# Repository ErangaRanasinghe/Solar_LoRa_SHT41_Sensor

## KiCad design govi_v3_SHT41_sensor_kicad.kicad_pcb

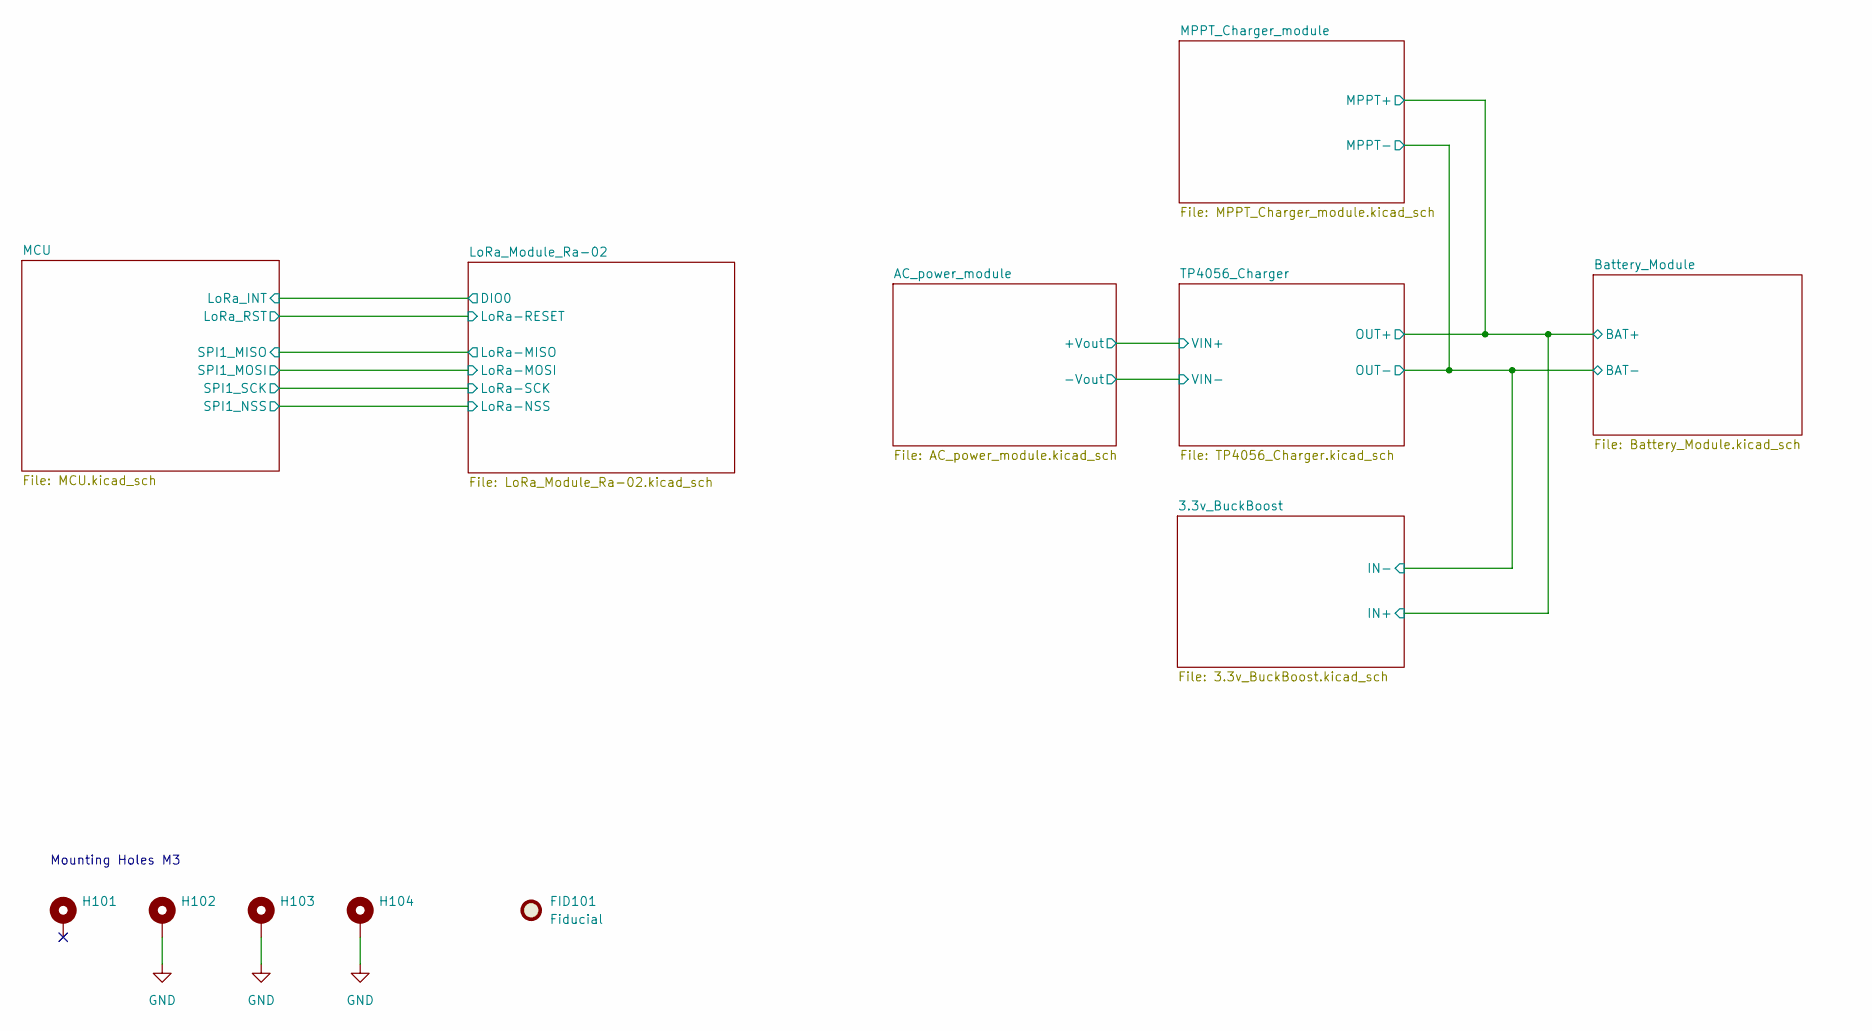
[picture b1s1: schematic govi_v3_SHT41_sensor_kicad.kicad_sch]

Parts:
FID101: Fiducial; Fiducial_1mm_Mask3mm
H101, H102, H103, H104: MountingHole_Pad; MountingHole_3.2mm_M3_Pad_TopBottom

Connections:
GND: H102.1, H103.1, H104.1; also elsewhere on the board

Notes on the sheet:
Mounting Holes M3

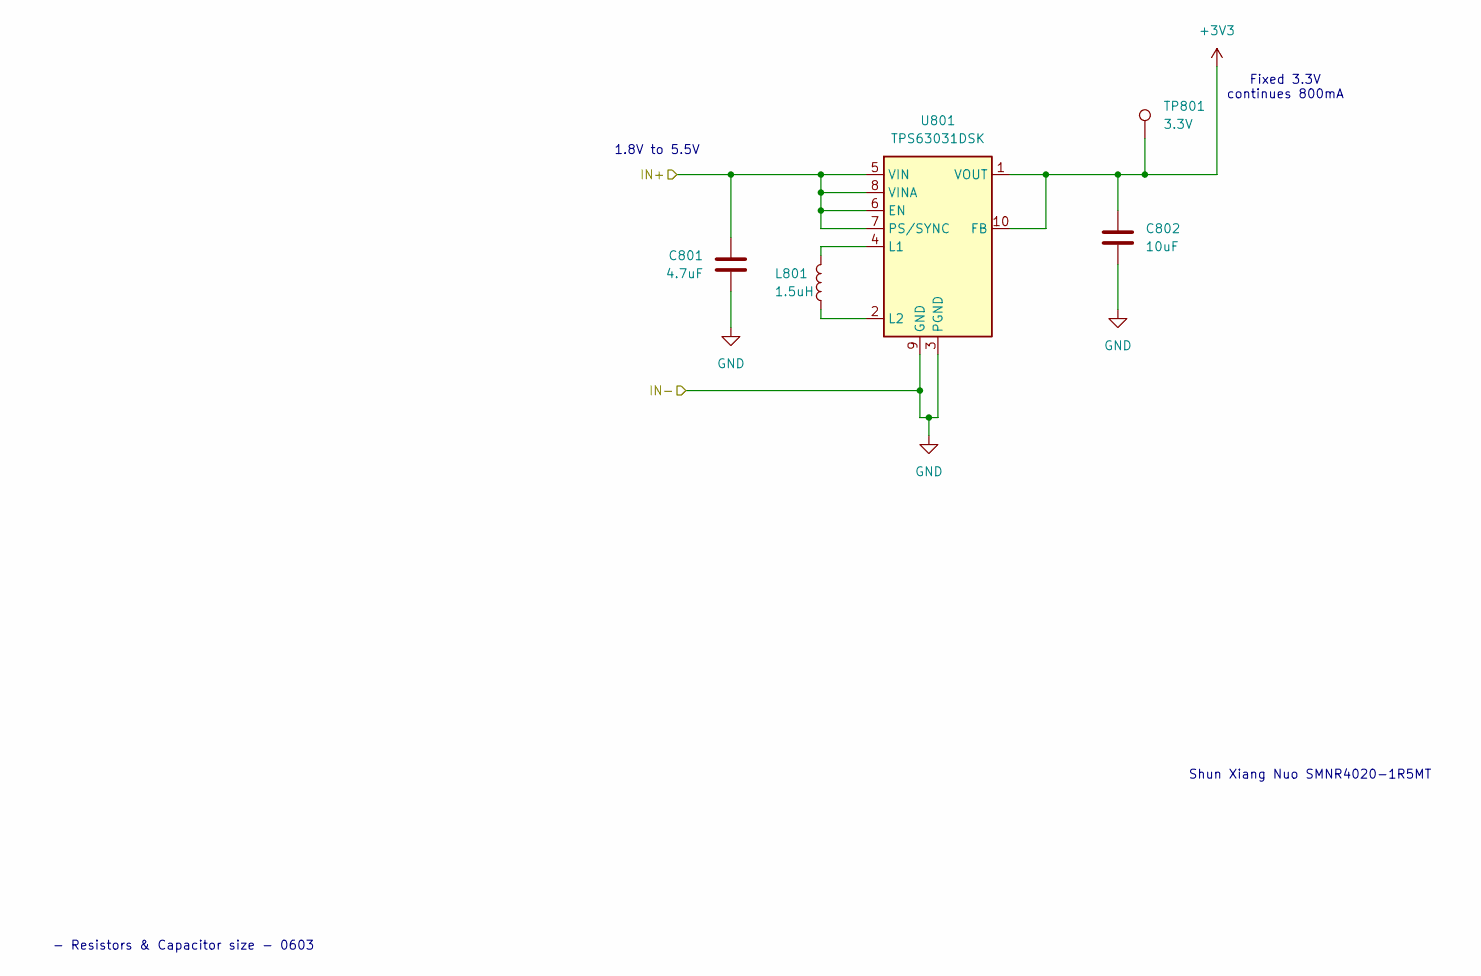
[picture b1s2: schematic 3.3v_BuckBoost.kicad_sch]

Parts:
C801: 4.7uF; C_0603_1608Metric_Pad1.08x0.95mm_HandSolder
C802: 10uF; C_0603_1608Metric_Pad1.08x0.95mm_HandSolder
L801: 1.5uH; L_Wurth_WE-LQSH-4020
TP801: 3.3V; TestPoint_Pad_D1.0mm
U801: TPS63031DSK; WSON-10-1EP_2.5x2.5mm_P0.5mm_EP1.2x2mm

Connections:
+3V3: C802.1, TP801.1, U801.1 (VOUT), U801.10 (FB); also elsewhere on the board
/3.3v_BuckBoost/IN+: C801.1, U801.5 (VIN), U801.6 (EN), U801.7 (PS/SYNC), U801.8 (VINA); also elsewhere on the board
GND: C801.2, C802.2, U801.3 (PGND), U801.9 (GND), U801.11 (PGND); also elsewhere on the board
unnamed: L801.1, U801.4 (L1)
unnamed: L801.2, U801.2 (L2)

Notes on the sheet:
Shun Xiang Nuo SMNR4020-1R5MT
- Resistors & Capacitor size - 0603
1.8V to 5.5V
Fixed 3.3V continues 800mA

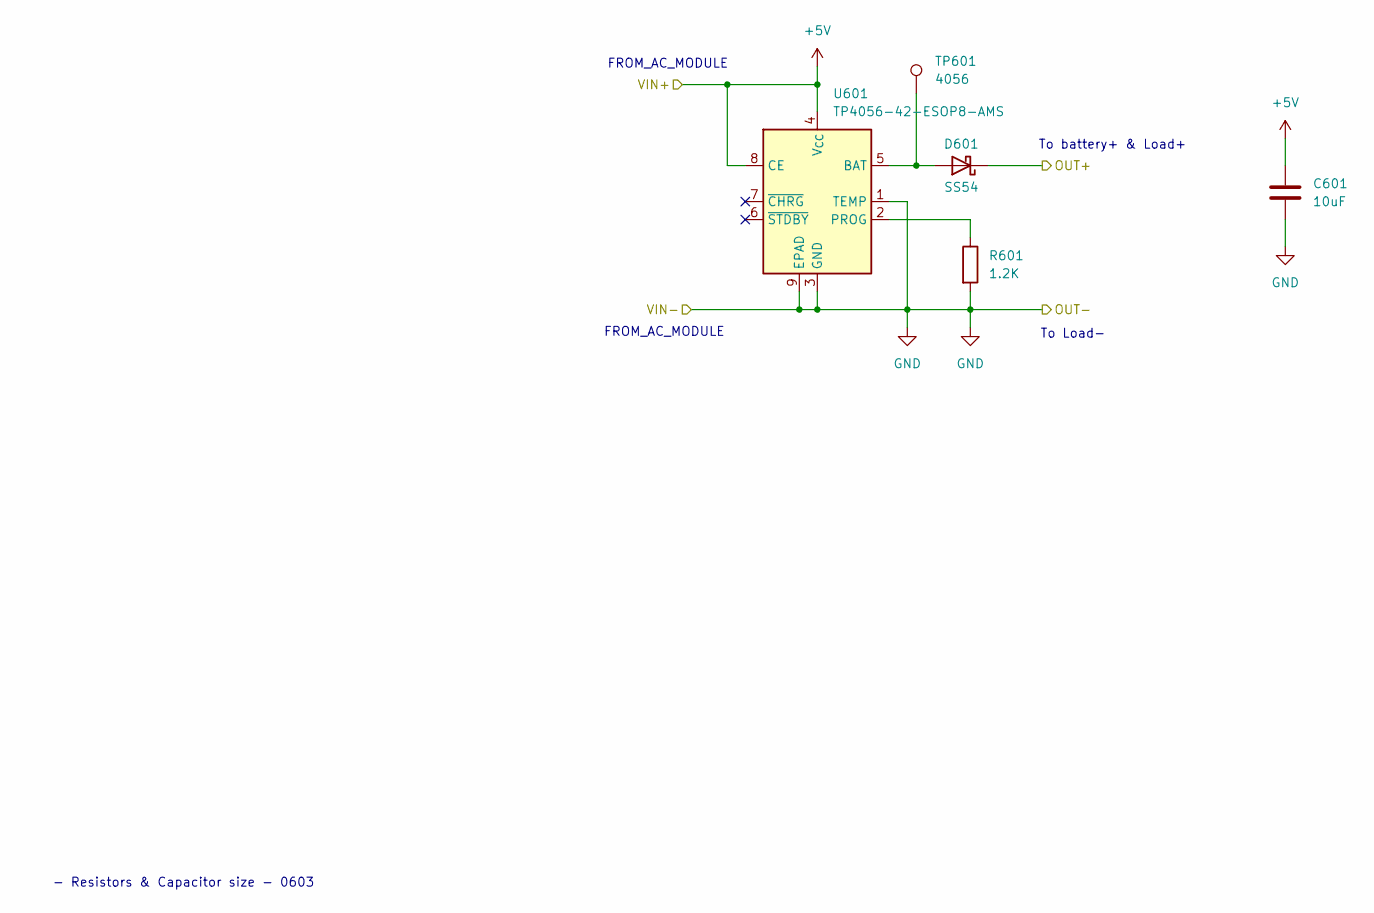
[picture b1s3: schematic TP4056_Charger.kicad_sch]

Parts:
C601: 10uF; C_0603_1608Metric_Pad1.08x0.95mm_HandSolder
D601: SS54; D_SMA
R601: 1.2K; R_0603_1608Metric_Pad0.98x0.95mm_HandSolder
TP601: 4056; TestPoint_Pad_D1.0mm
U601: TP4056-42-ESOP8-AMS; SOIC-8-1EP_3.9x4.9mm_P1.27mm_EP2.41x3.3mm_ThermalVias

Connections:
+5V: C601.1, U601.4 (V_{CC}), U601.8 (CE); also elsewhere on the board
/3.3v_BuckBoost/IN+: D601.1 (K); also elsewhere on the board
GND: C601.2, R601.2, U601.1 (TEMP), U601.3 (GND), U601.9 (EPAD); also elsewhere on the board
unnamed: D601.2 (A), TP601.1, U601.5 (BAT)
unnamed: R601.1, U601.2 (PROG)

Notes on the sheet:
- Resistors & Capacitor size - 0603
To battery+ & Load+
To Load-
FROM_AC_MODULE

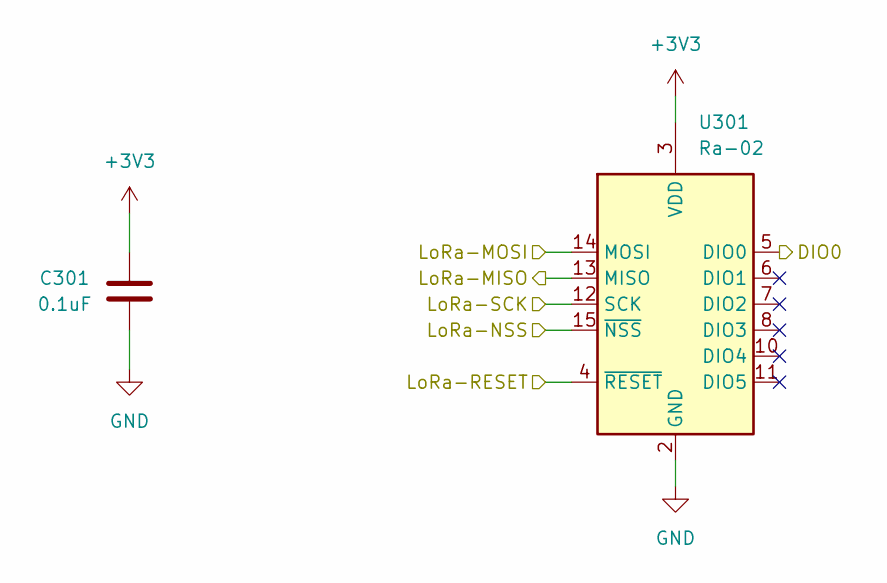
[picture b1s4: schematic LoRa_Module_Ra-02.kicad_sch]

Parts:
C301: 0.1uF; C_0402_1005Metric_Pad0.74x0.62mm_HandSolder
U301: Ra-02; Ai-Thinker-Ra-01-LoRa

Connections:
+3V3: C301.1, U301.3 (VDD); also elsewhere on the board
/LoRa_Module_Ra-02/LoRa-MISO: U301.13 (MISO); also elsewhere on the board
/LoRa_Module_Ra-02/LoRa-MOSI: U301.14 (MOSI); also elsewhere on the board
/LoRa_Module_Ra-02/LoRa-NSS: U301.15 (~NSS); also elsewhere on the board
/LoRa_Module_Ra-02/LoRa-RESET: U301.4 (~RESET); also elsewhere on the board
/LoRa_Module_Ra-02/LoRa-SCK: U301.12 (SCK); also elsewhere on the board
/MCU/LoRa_INT: U301.5 (DIO0); also elsewhere on the board
GND: C301.2, U301.1 (GND), U301.2 (GND), U301.9 (GND), U301.16 (GND); also elsewhere on the board

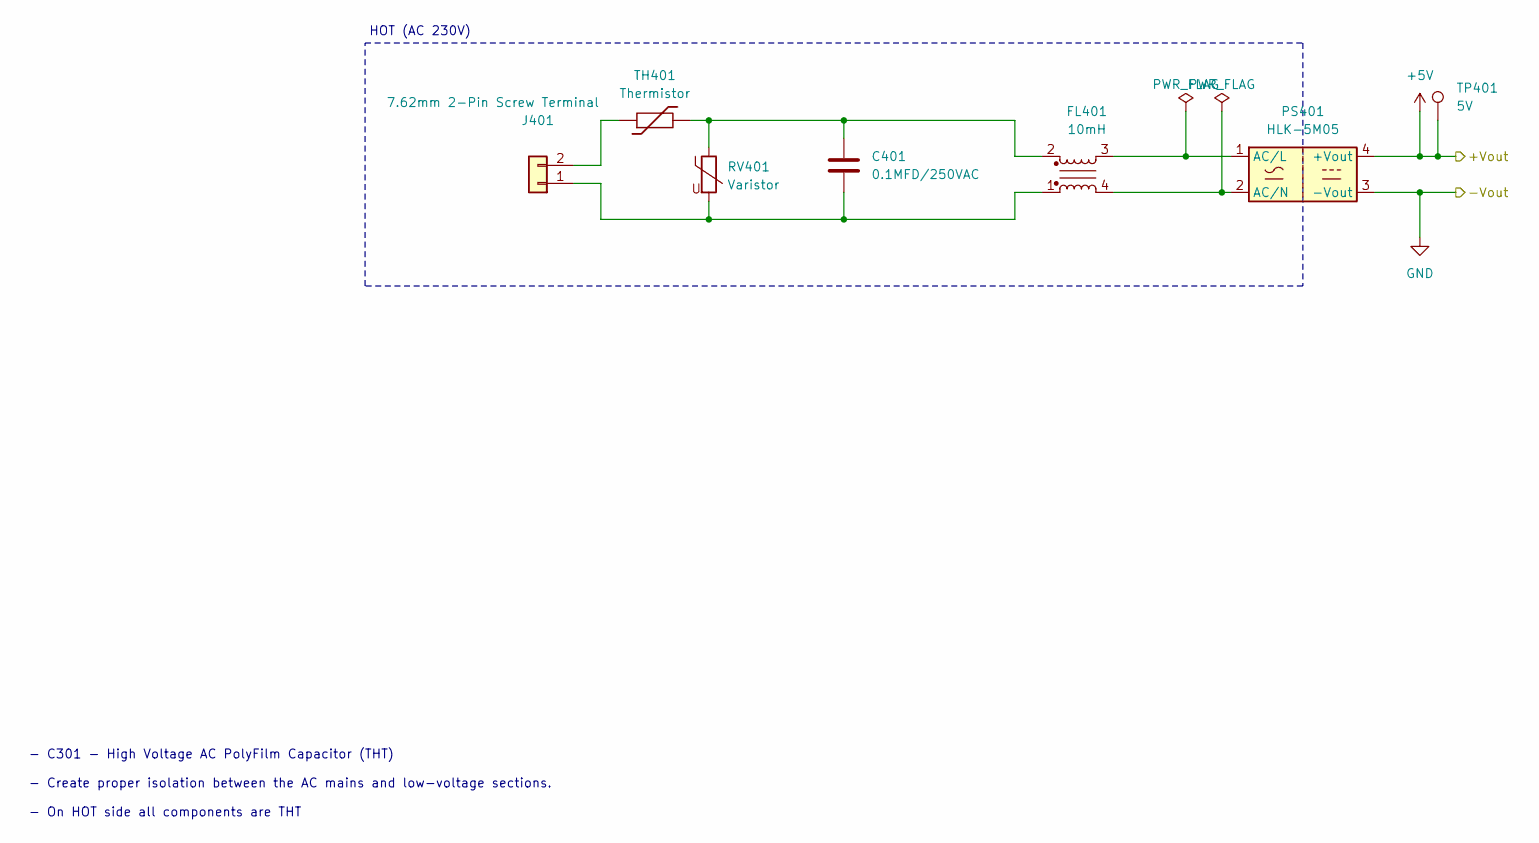
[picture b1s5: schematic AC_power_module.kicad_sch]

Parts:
C401: 0.1MFD/250VAC; C_Rect_L11.5mm_W5.0mm_P10.00mm_MKT
FL401: 10mH; B82730U3451A020-ferrite-core-inductor
J401: 7.62mm 2-Pin Screw Terminal; P=7.62mm Barrier Terminal Blocks azend
PS401: HLK-5M05; HLK5M05
RV401: Varistor; RV_Disc_D12mm_W5.1mm_P7.5mm
TH401: Thermistor; B57236S0250M000-Thermister
TP401: 5V; TestPoint_Pad_D1.0mm

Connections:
+5V: PS401.4 (+Vout), TP401.1; also elsewhere on the board
GND: PS401.3 (-Vout); also elsewhere on the board
unnamed: C401.1, FL401.2, RV401.1, TH401.2
unnamed: C401.2, FL401.1, J401.1, RV401.2
unnamed: J401.2, TH401.1
unnamed: FL401.3, PS401.1 (AC/L)
unnamed: FL401.4, PS401.2 (AC/N)

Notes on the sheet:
HOT (AC 230V)
- C301 - High Voltage AC PolyFilm Capacitor (THT) - Create proper isolation between the AC mains and low-voltage sections. - On HOT side all components are THT

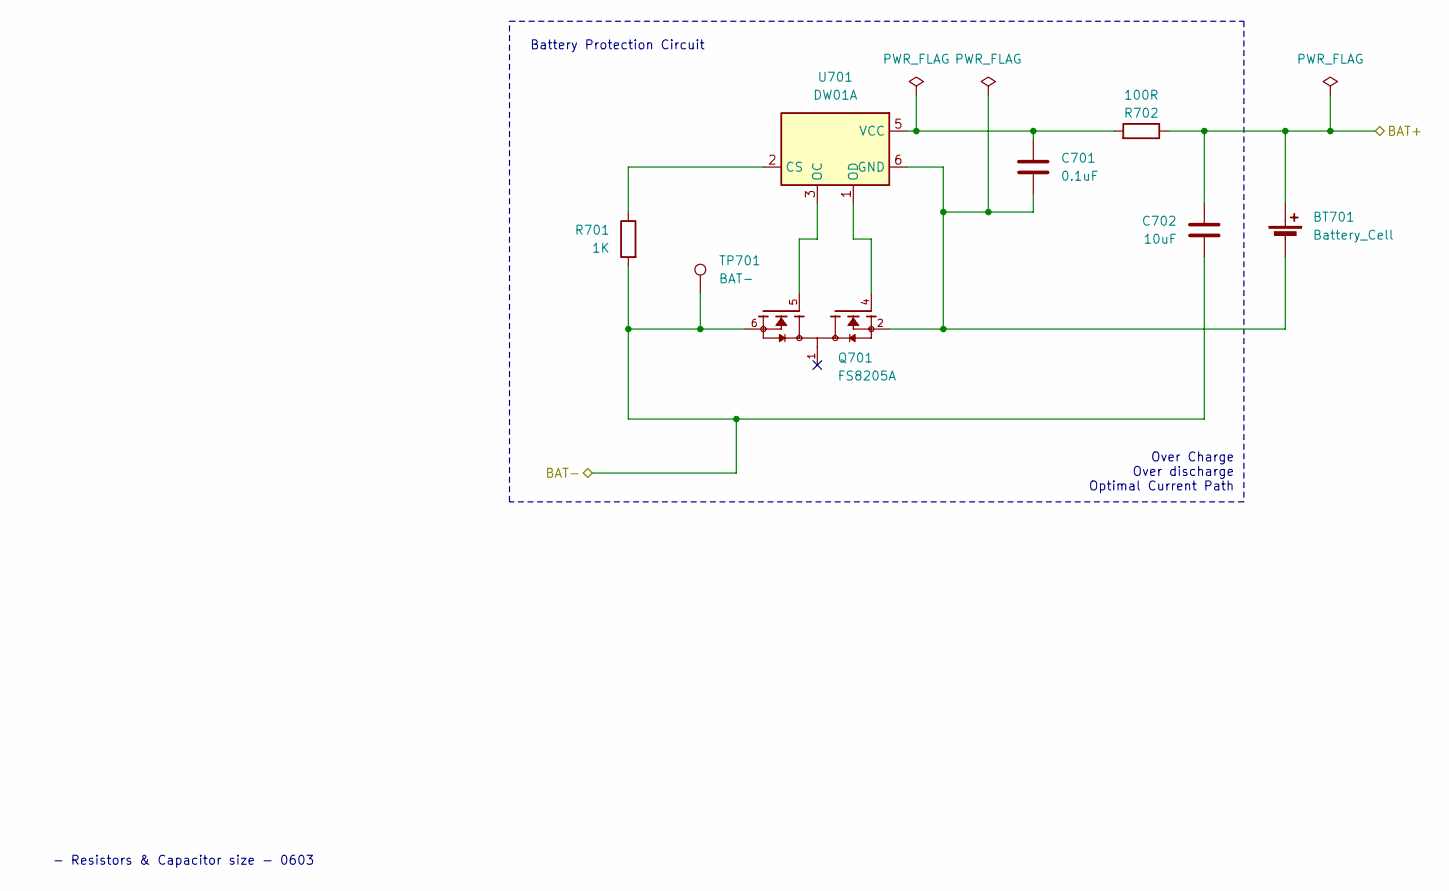
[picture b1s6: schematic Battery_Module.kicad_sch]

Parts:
BT701: Battery_Cell; BAT_1042P
C701: 0.1uF; C_0603_1608Metric_Pad1.08x0.95mm_HandSolder
C702: 10uF; C_0603_1608Metric_Pad1.08x0.95mm_HandSolder
Q701: FS8205A; SOP65P640X120-8N; PARTREV 1.7
R701: 1K; R_0603_1608Metric_Pad0.98x0.95mm_HandSolder
R702: 100R; R_0603_1608Metric_Pad0.98x0.95mm_HandSolder
TP701: BAT-; TestPoint_Pad_D1.0mm
U701: DW01A; SOT-23-6

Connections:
/3.3v_BuckBoost/IN+: BT701.1 (+), C702.1, R702.1; also elsewhere on the board
GND: C702.2, Q701.6, Q701.7, R701.2, TP701.1; also elsewhere on the board
unnamed: BT701.2 (-), C701.2, Q701.2, Q701.3, U701.6 (GND)
unnamed: R701.1, U701.2 (CS)
unnamed: Q701.5, U701.3 (OC)
unnamed: Q701.4, U701.1 (OD)
unnamed: C701.1, R702.2, U701.5 (VCC)

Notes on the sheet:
Over Charge Over discharge Optimal Current Path
- Resistors & Capacitor size - 0603
Battery Protection Circuit

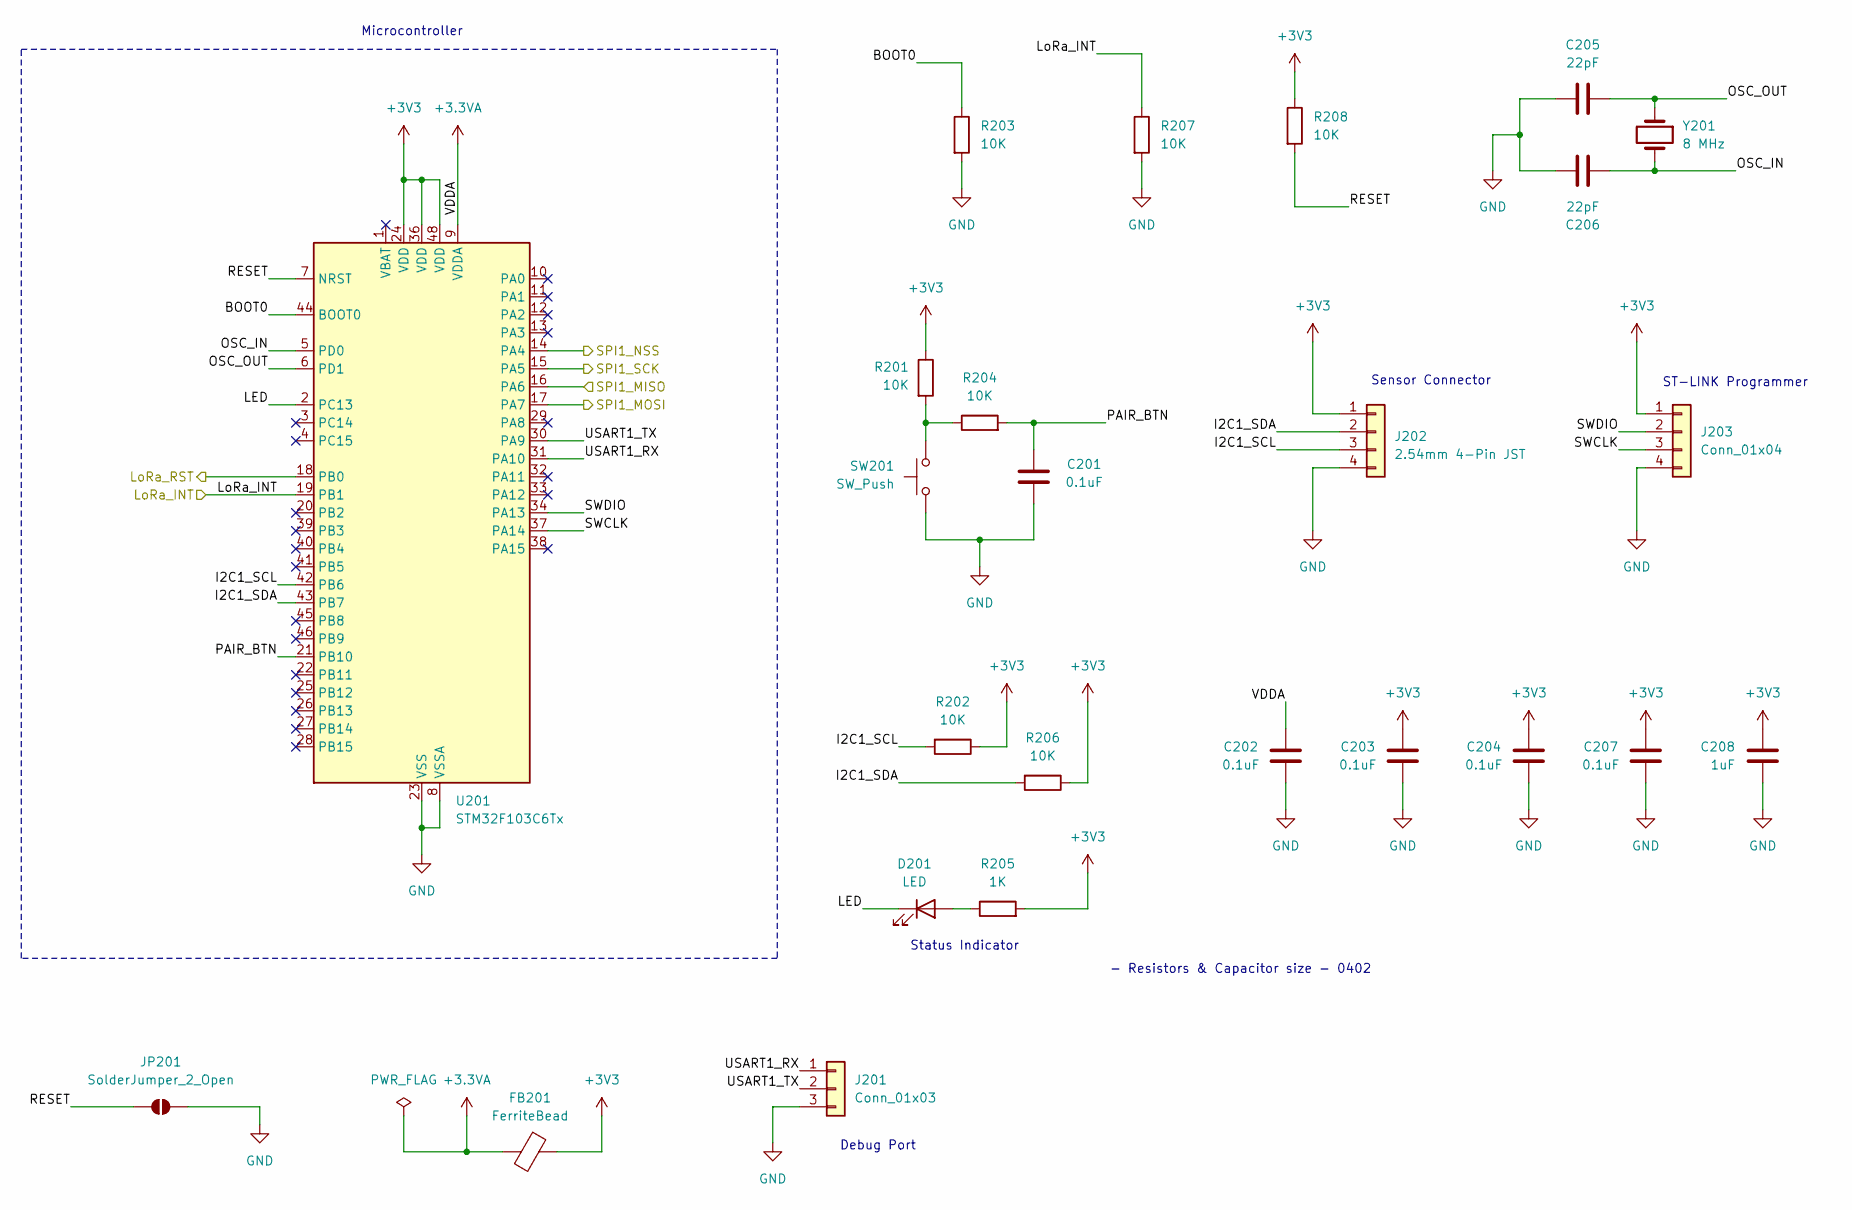
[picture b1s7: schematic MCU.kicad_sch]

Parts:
C201, C202, C203, C204, C207: 0.1uF; C_0402_1005Metric_Pad0.74x0.62mm_HandSolder
C205, C206: 22pF; C_0402_1005Metric_Pad0.74x0.62mm_HandSolder
C208: 1uF; C_0402_1005Metric_Pad0.74x0.62mm_HandSolder
D201: LED; LED_D3.0mm
FB201: FerriteBead; R_0402_1005Metric_Pad0.72x0.64mm_HandSolder
J201: Conn_01x03; PinHeader_1x03_P2.54mm_Vertical
J202: 2.54mm 4-Pin JST; JST_EH_B4B-EH-A_1x04_P2.50mm_Vertical
J203: Conn_01x04; PinHeader_1x04_P2.54mm_Vertical
JP201: SolderJumper_2_Open; SolderJumper-2_P1.3mm_Open_RoundedPad1.0x1.5mm
R201, R202, R203, R204, R206, R207, R208: 10K; R_0402_1005Metric_Pad0.72x0.64mm_HandSolder
R205: 1K; R_0402_1005Metric_Pad0.72x0.64mm_HandSolder
SW201: SW_Push; PinHeader_1x02_P2.54mm_Vertical
U201: STM32F103C6Tx; LQFP-48_7x7mm_P0.5mm
Y201: 8 MHz; Crystal_HC49-4H_Vertical

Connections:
+3.3VA: C202.1, FB201.2, U201.9 (VDDA)
+3V3: C203.1, C204.1, C207.1, C208.1, FB201.1, J202.1, J203.1, R201.1, R202.1, R205.2, R206.1, R208.1, U201.24 (VDD), U201.36 (VDD), U201.48 (VDD); also elsewhere on the board
/LoRa_Module_Ra-02/LoRa-MISO: U201.16 (PA6); also elsewhere on the board
/LoRa_Module_Ra-02/LoRa-MOSI: U201.17 (PA7); also elsewhere on the board
/LoRa_Module_Ra-02/LoRa-NSS: U201.14 (PA4); also elsewhere on the board
/LoRa_Module_Ra-02/LoRa-RESET: U201.18 (PB0); also elsewhere on the board
/LoRa_Module_Ra-02/LoRa-SCK: U201.15 (PA5); also elsewhere on the board
/MCU/BOOT0: R203.1, U201.44 (BOOT0)
/MCU/I2C1_SCL: J202.3, R202.2, U201.42 (PB6)
/MCU/I2C1_SDA: J202.2, R206.2, U201.43 (PB7)
/MCU/LED: D201.1 (K), U201.2 (PC13)
/MCU/LoRa_INT: R207.1, U201.19 (PB1); also elsewhere on the board
/MCU/OSC_IN: C206.1, U201.5 (PD0), Y201.2
/MCU/OSC_OUT: C205.1, U201.6 (PD1), Y201.1
/MCU/PAIR_BTN: C201.1, R204.2, U201.21 (PB10)
/MCU/RESET: JP201.1 (A), R208.2, U201.7 (NRST)
/MCU/SWCLK: J203.3, U201.37 (PA14)
/MCU/SWDIO: J203.2, U201.34 (PA13)
/MCU/USART1_RX: J201.1, U201.31 (PA10)
/MCU/USART1_TX: J201.2, U201.30 (PA9)
GND: C201.2, C202.2, C203.2, C204.2, C205.2, C206.2, C207.2, C208.2, J201.3, J202.4, J203.4, JP201.2 (B), R203.2, R207.2, SW201.1, U201.8 (VSSA), U201.23 (VSS), U201.35 (VSS), U201.47 (VSS); also elsewhere on the board
unnamed: D201.2 (A), R205.1
unnamed: R201.2, R204.1, SW201.2

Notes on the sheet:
Status Indicator
Debug Port
Sensor Connector
- Resistors & Capacitor size - 0402
ST-LINK Programmer
Microcontroller

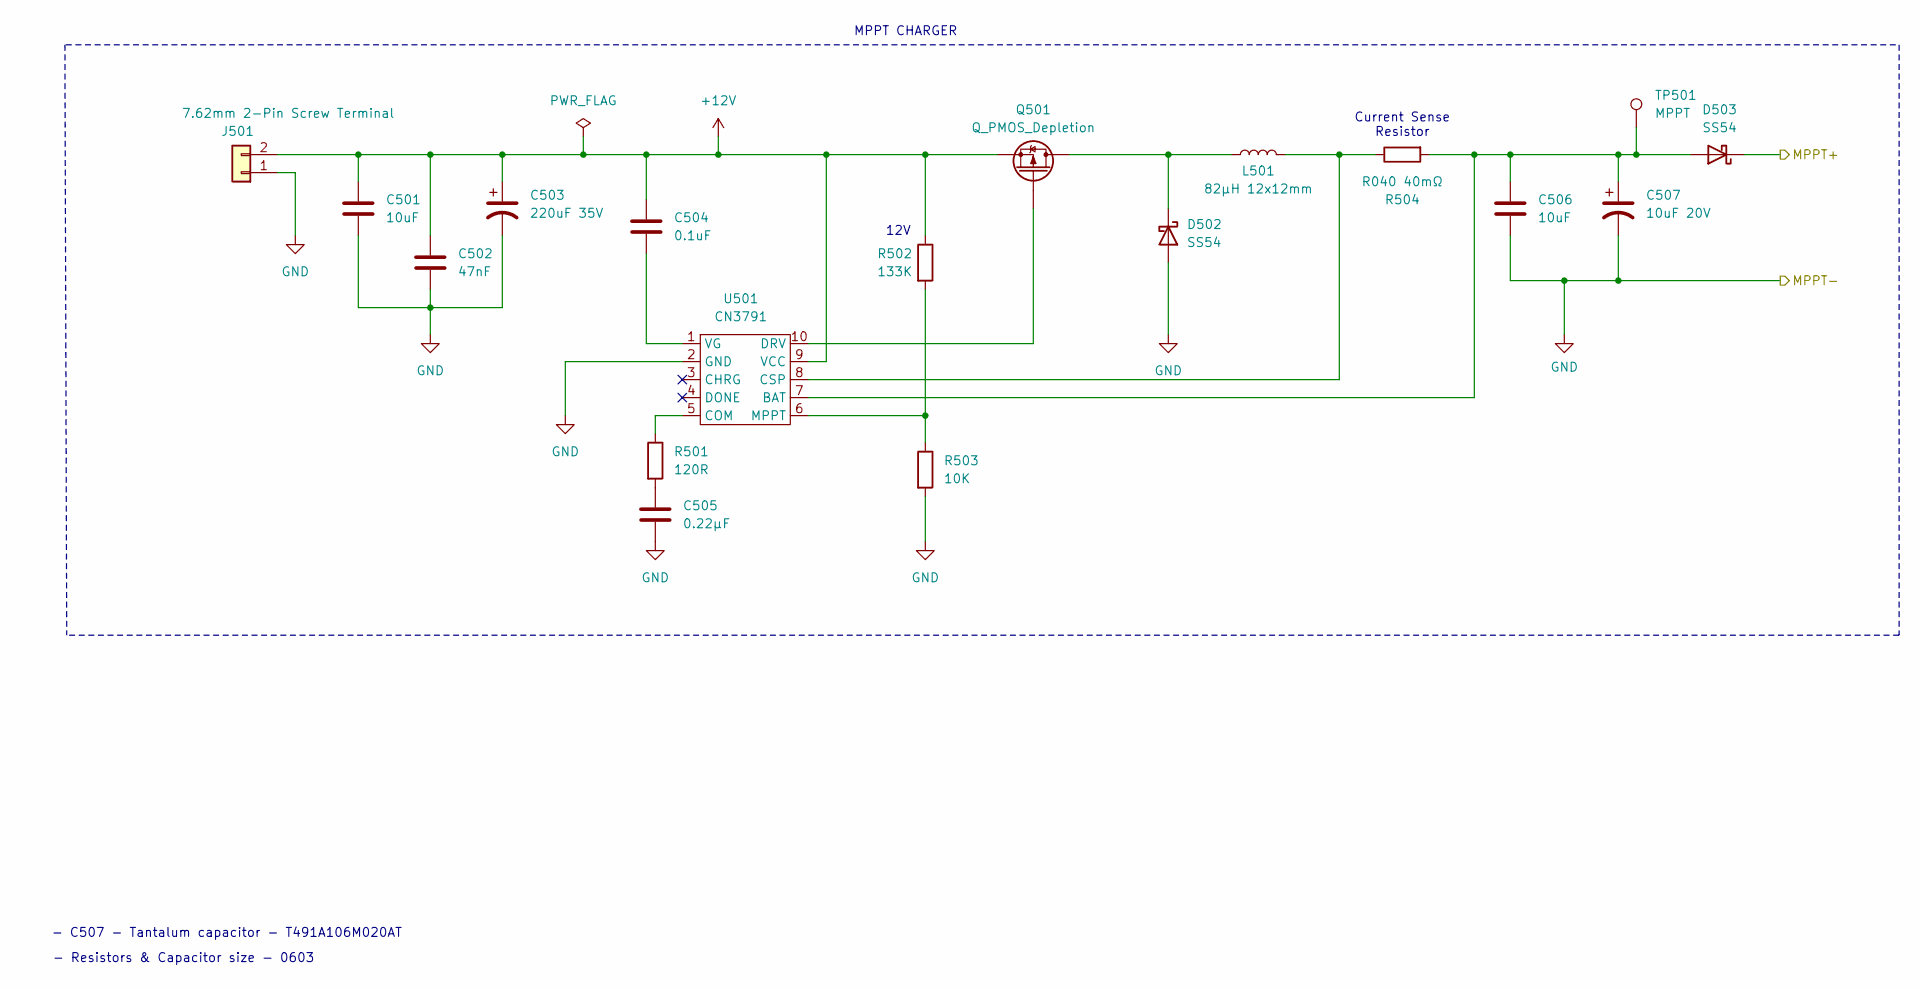
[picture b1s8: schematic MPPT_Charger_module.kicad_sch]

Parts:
C501, C506: 10uF; C_0603_1608Metric_Pad1.08x0.95mm_HandSolder
C502: 47nF; C_0603_1608Metric_Pad1.08x0.95mm_HandSolder
C503: 220uF 35V; CP_Elec_6.3x7.7
C504: 0.1uF; C_0603_1608Metric_Pad1.08x0.95mm_HandSolder
C505: 0.22µF; C_0603_1608Metric_Pad1.08x0.95mm_HandSolder
C507: 10uF 20V; CP_EIA-3216-18_Kemet-A_HandSolder
D502, D503: SS54; D_SMA
J501: 7.62mm 2-Pin Screw Terminal; P=7.62mm Barrier Terminal Blocks azend
L501: 82µH 12x12mm; L_12x12mm_H4.5mm
Q501: Q_PMOS_Depletion; TO-252-2
R501: 120R; R_0603_1608Metric_Pad0.98x0.95mm_HandSolder
R502: 133K; R_0603_1608Metric_Pad0.98x0.95mm_HandSolder
R503: 10K; R_0603_1608Metric_Pad0.98x0.95mm_HandSolder
R504: R040 40mΩ; R_2512_6332Metric_Pad1.40x3.35mm_HandSolder
TP501: MPPT; TestPoint_Pad_D1.0mm
U501: CN3791; SSOP-10_3.9x4.9mm_P1.00mm

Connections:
+12V: C501.1, C502.1, C503.1, C504.1, J501.2, Q501.3 (S), R502.1, U501.9 (VCC)
/3.3v_BuckBoost/IN+: D503.1 (K); also elsewhere on the board
GND: C501.2, C502.2, C503.2, C505.2, C506.2, C507.2, D502.2 (A), J501.1, R503.2, U501.2 (GND); also elsewhere on the board
unnamed: C505.1, R501.2
unnamed: D502.1 (K), L501.1, Q501.2 (D)
unnamed: C506.1, C507.1, D503.2 (A), R504.2, TP501.1, U501.7 (BAT)
unnamed: Q501.1 (G), U501.10 (DRV)
unnamed: R501.1, U501.5 (COM)
unnamed: L501.2, R504.1, U501.8 (CSP)
unnamed: R502.2, R503.1, U501.6 (MPPT)
unnamed: C504.2, U501.1 (VG)

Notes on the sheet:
Current Sense Resistor
12V
- C507 - Tantalum capacitor - T491A106M020AT
- Resistors & Capacitor size - 0603
MPPT CHARGER

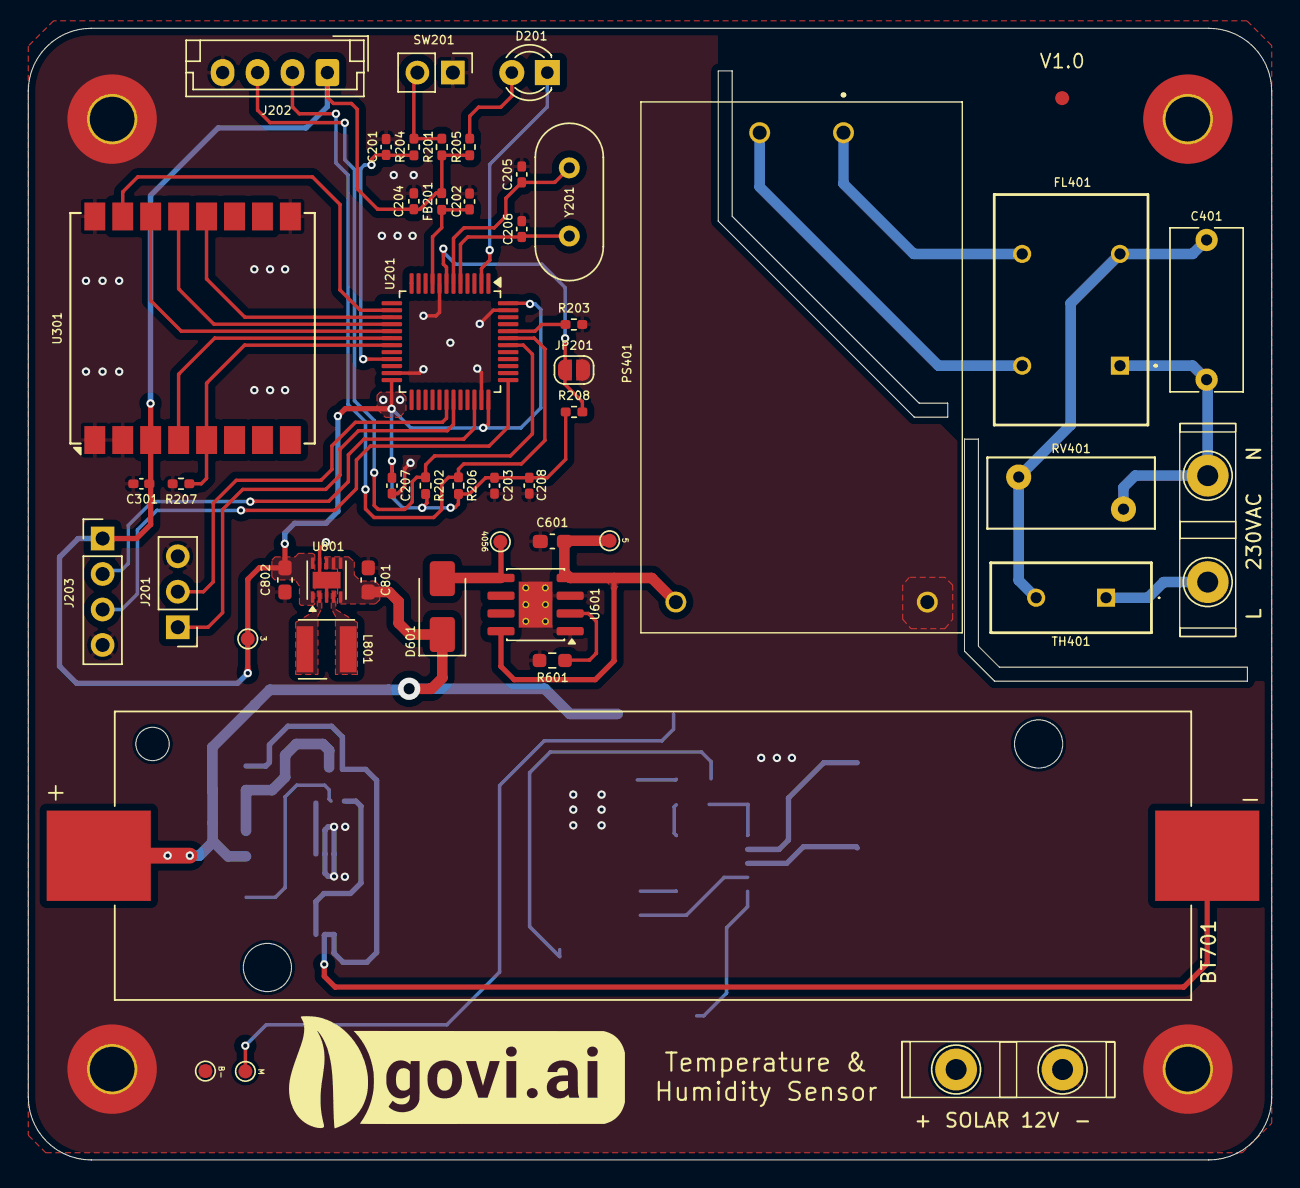
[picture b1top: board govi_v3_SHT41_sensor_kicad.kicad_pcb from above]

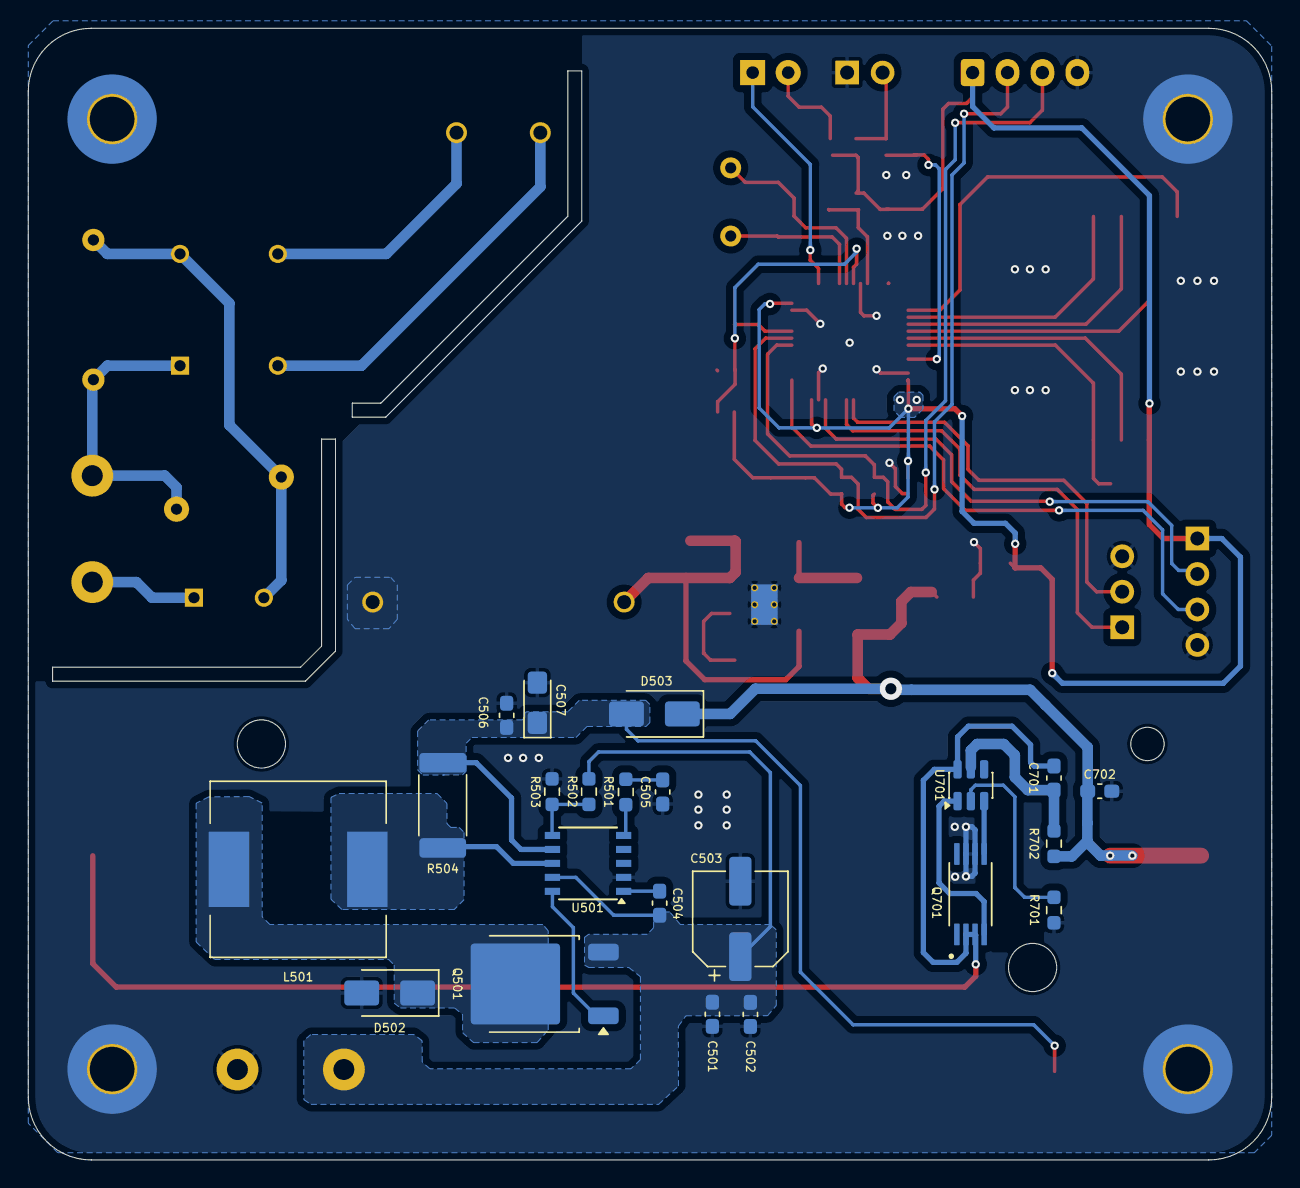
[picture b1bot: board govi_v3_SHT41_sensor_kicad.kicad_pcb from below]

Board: 2 copper layers, 89.0 x 81.0 mm, 75 parts (22 on the bottom side), 48 nets.

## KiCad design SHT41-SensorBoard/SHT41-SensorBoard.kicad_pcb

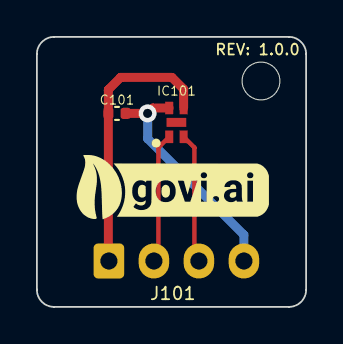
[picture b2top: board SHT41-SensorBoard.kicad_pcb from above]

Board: 2 copper layers, 15.0 x 15.0 mm, 5 parts (0 on the bottom side), 4 nets.

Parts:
C101: C; C_0402_1005Metric
G1: GOVI.AI-LOGO-FRONT; govi-ai-logo-front-for-sensor
H101: M2.5; MountingHole_2.1mm
IC101: SHT41A-AD1B-R2; SON80P150X150X59-5N
J101: 2.54mm 4-Pin JST; JST_EH_B4B-EH-A_1x04_P2.50mm_Vertical

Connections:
+3V3: C101.1, IC101.3 (VDD), J101.1
/I2C-SCL: IC101.2 (SCL), J101.3
/I2C-SDA: IC101.1 (SDA), J101.2
GND: C101.2, IC101.4 (VSS), J101.4

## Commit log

2025-11-30 "initial commit schematic design"
2025-12-02 "3.3V buck boost converter added. few footprints added"
2025-12-02 "Assign Footprints Done"
2025-12-02 "Some Component values were changed in MPPT sheet"
2025-12-03 "I2c Pin change. PB6:SCL1 , PB7:SDA1"
2025-12-03 "Debug port added in schematic"
2025-12-04 "PCB front Layer Component assembly done"
2025-12-06 "Working on Routing MCU"
2025-12-06 "Before changing the orientation of the LoRa module. removing existing LoRa module routing."
2025-12-08 "Routing done. DRC pending"
